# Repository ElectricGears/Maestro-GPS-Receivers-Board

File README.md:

Maestro-GPS-Receivers-Board
===========================

Breadboard Adapter for A2200-A GPS Receiver

This is .7" wide breadboard adapter for the Mestro A2200-A GPS Receiver module for eaiser prototyping. Available at http://www.maestro-wireless.com/a-2200-a

There is an on board vertical SMA connector (Amphenol Connex #132134). The trace to the antenna is .8mm wide with .3mm clearance to surrounding ground plane. I don't have an RF design knowledge so I used the width of the edge connector on the GPS module. An equation in the data sheet calls for 2.88mm trace and the clearance was not given. I made this for a user on Reddit so I don't actually have the GPS module and have not verified the dimensions or it's performance.

Made in KiCAD Version: (2013-07-07 BZR 4022)-stable

Released under Creative Commons Attribution-ShareAlike 4.0 International (CC BY-SA 4.0) 
https://creativecommons.org/licenses/by-sa/4.0/

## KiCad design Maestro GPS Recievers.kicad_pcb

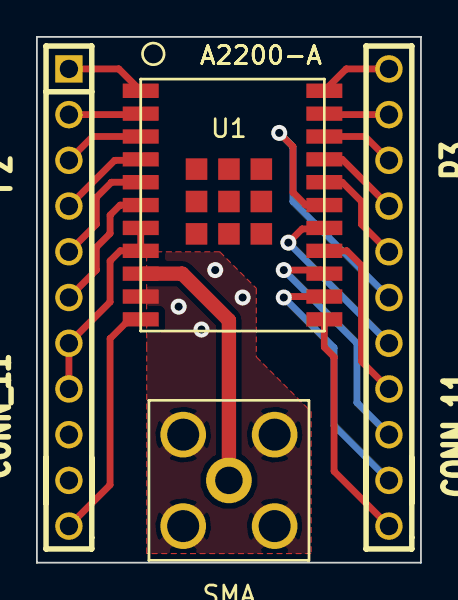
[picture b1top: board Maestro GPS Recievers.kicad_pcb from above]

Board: 2 copper layers, 21.3 x 29.2 mm, 4 parts (0 on the bottom side), 21 nets.

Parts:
P1: SMA; SMA_Vertical
P2, P3: CONN_11; SIL-11
U1: A2200-A

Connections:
ANT_GND: P1.2, U1.10
ANT_IN: P2.11, U1.11
ExtInt: P3.10, U1.13
ExtInt/GPIO 8: P2.5, U1.5
GND: P2.7, P2.8, U1.7, U1.8
GPIO2: P2.1, U1.1
GPIO 3: P3.11, U1.12
GPIO 6: P3.6, U1.17
GPIO 7: P3.5, U1.18
I2C_CLK: P3.8, U1.15
I2C_DI 0: P3.7, U1.16
NC: P3.2, U1.21
ON/OFF: P2.6, U1.6
RX 0: P2.4, U1.4
TM/GPIO 5: P3.9, U1.14
TX 0: P2.3, U1.3
VANT: P1.1, U1.9
Vcc3.3V: P3.3, U1.20
Vout: P2.2, U1.2
WAKEUP: P3.4, U1.19
nRST: P3.1, U1.22

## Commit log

2014-03-07 Initial files
2014-03-07 board image
